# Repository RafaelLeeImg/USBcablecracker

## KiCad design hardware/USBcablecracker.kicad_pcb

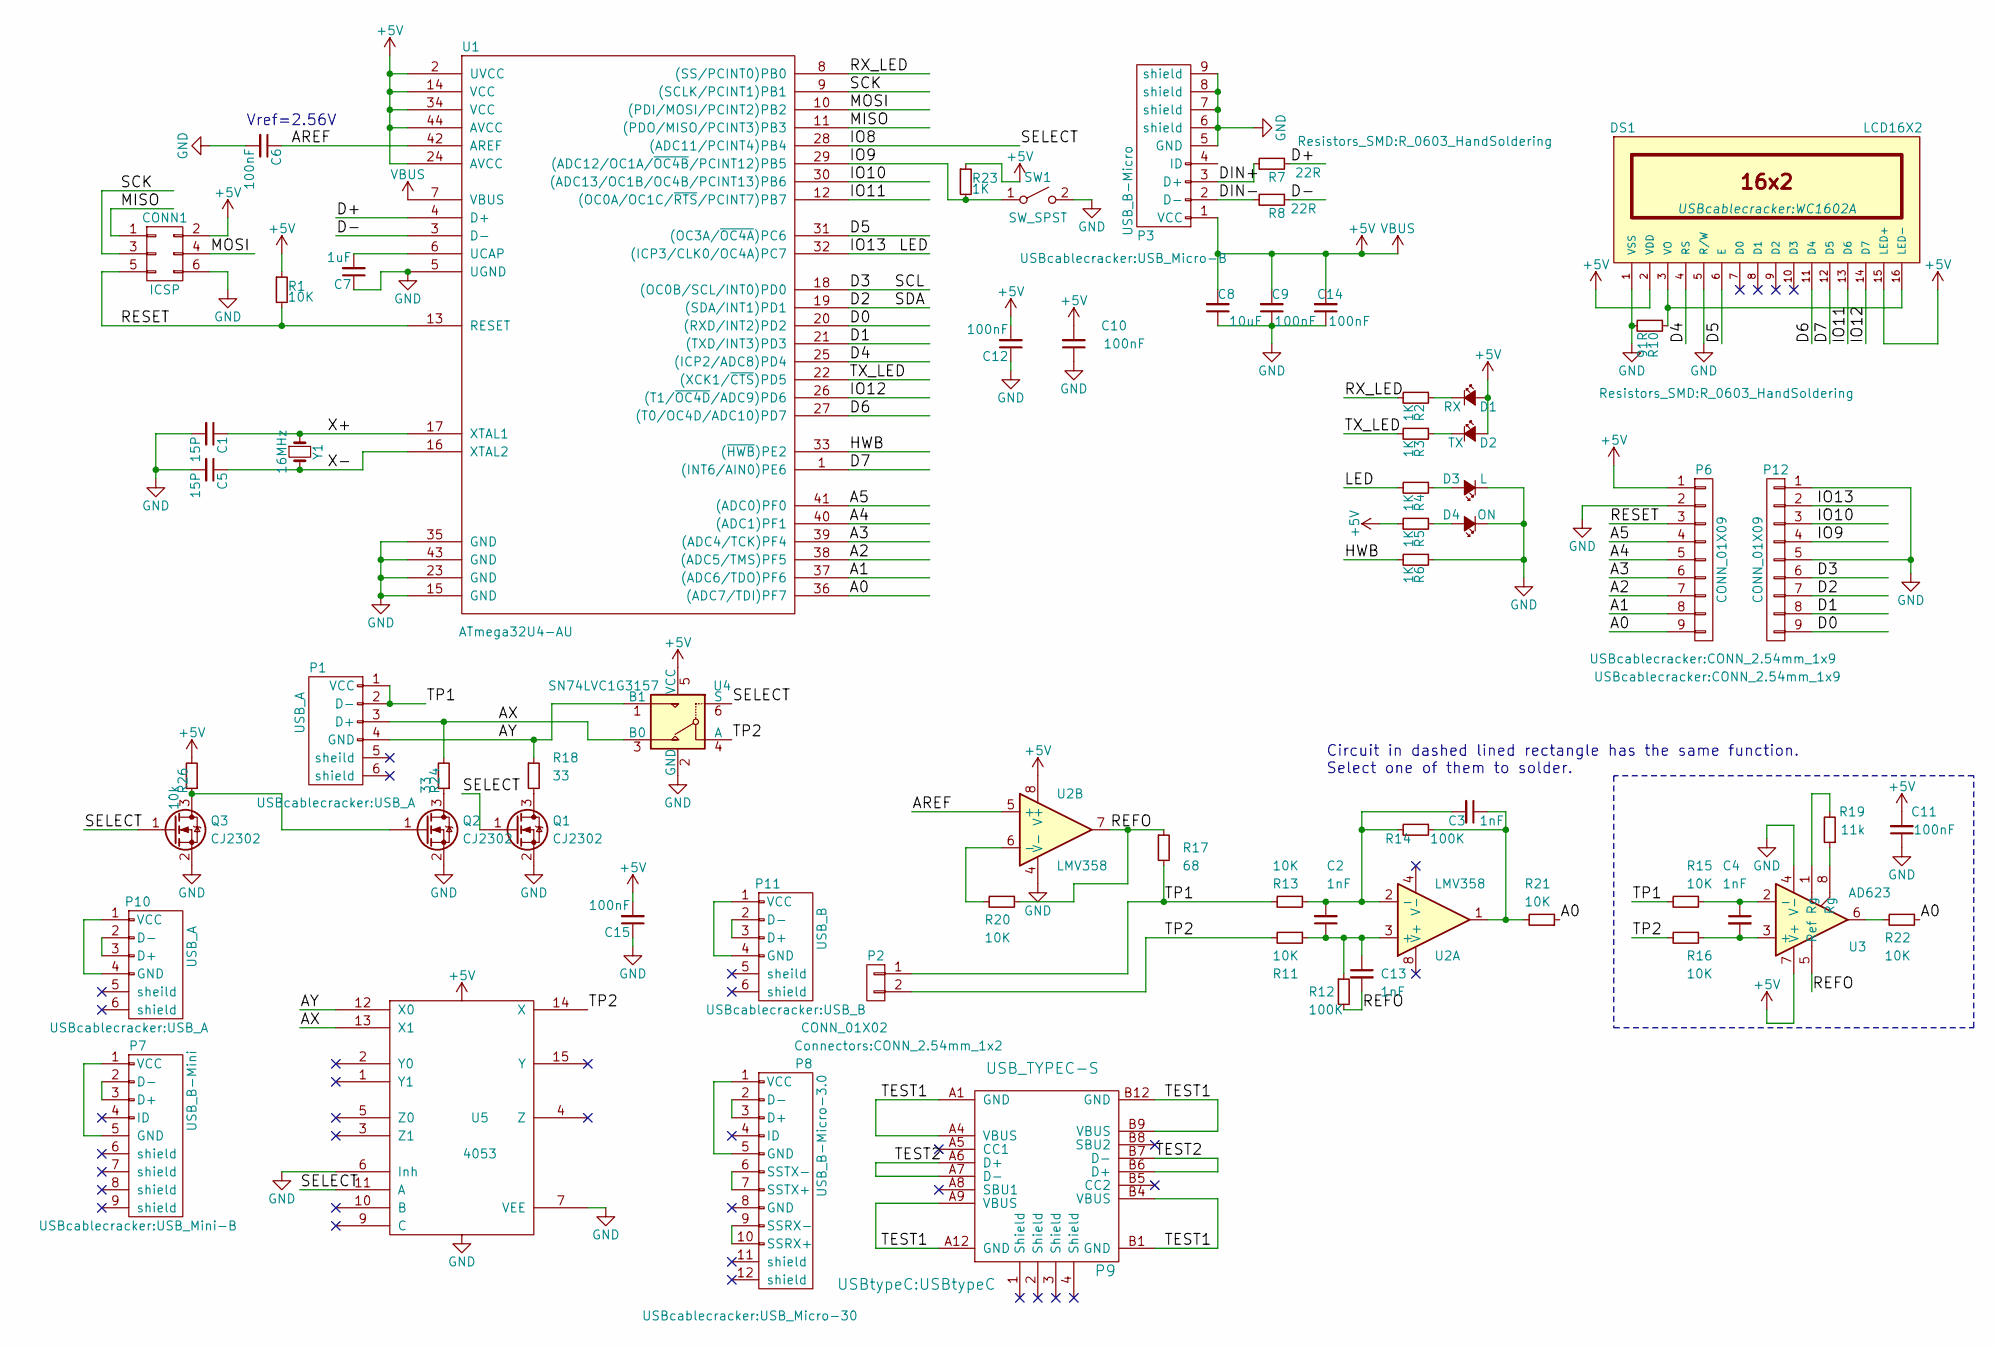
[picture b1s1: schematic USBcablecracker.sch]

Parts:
C1, C5: 15P; C_0603_HandSoldering
C2, C3, C4, C13: 1nF; C_0603_HandSoldering
C6, C9, C10, C11, C12, C14, C15: 100nF; C_0603_HandSoldering
C7: 1uF; C_0603_HandSoldering
C8: 10uF; C_0603_HandSoldering
CONN1: ICSP; CONN_2.54mm_2x3
D1: RX; LED_0603
D2: TX; LED_0603
D3: L; LED_0603
D4: ON; LED_0603
DS1: LCD16X2; WC1602A
P1, P10: USB_A
P2: CONN_01X02; CONN_2.54mm_1x2
P3: USB_B-Micro; USB_Micro-B
P6, P12: CONN_01X09; CONN_2.54mm_1x9
P7: USB_B-Mini; USB_Mini-B
P8: USB_B-Micro-3.0; USB_Micro-30
P9: USB_TYPEC-S; USBtypeC
P11: USB_B
Q1, Q2, Q3: CJ2302; SOT-23_Handsoldering
R1, R11, R13, R15, R16, R20, R21, R22: 10K; R_0603_HandSoldering
R2, R3, R4, R5, R6, R23: 1K; R_0603_HandSoldering
R7, R8: 22R; R_0603_HandSoldering
R10: 91R; R_0603_HandSoldering
R12, R14: 100K; R_0603_HandSoldering
R17: 68; R_0603_HandSoldering
R18, R24: 33; R_0603_HandSoldering
R19: 11k; R_0603_HandSoldering
R26: 10k; R_0603_HandSoldering
SW1: SW_SPST; SW_SPST_EVQP0
U1: ATmega32U4-AU; TQFP-44_10x10mm_Pitch0.8mm
U2: LMV358; SOIC-8_3.9x4.9mm_Pitch1.27mm
U3: AD623; SOIC-8_3.9x4.9mm_Pitch1.27mm
U4: SN74LVC1G3157; SOT-23-6_Handsoldering
U5: 4053; TSSOP-16_4.4x5mm_Pitch0.65mm
Y1: 16MHz; crystal_FA238-TSX3225

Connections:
+5C: C8.2, C9.2, C10.2, C11.2, C12.2, C14.2, C15.2, CONN1.2, D1.2 (A), D2.2 (A), DS1.2 (VDD), DS1.15 (LED+), P3.1 (VCC), P6.1, R1.1, R5.2, R23.1, R26.2, U1.2 (UVCC), U1.7 (VBUS), U1.14 (VCC), U1.24 (AVCC), U1.34 (VCC), U1.44 (AVCC), U2.8 (V+), U3.7 (V+), U4.5 (VCC), U5.16 (VDD)
/A0: P6.9, R21.1, R22.1, U1.36 ((ADC7/TDI)PF7)
/A1: P6.8, U1.37 ((ADC6/TDO)PF6)
/A2: P6.7, U1.38 ((ADC5/TMS)PF5)
/A3: P6.6, U1.39 ((ADC4/TCK)PF4)
/A4: P6.5, U1.40 ((ADC1)PF1)
/A5: P6.4, U1.41 ((ADC0)PF0)
/AREF: C6.1, U1.42 (AREF), U2.5 (+)
/AX: P1.3 (D+), R24.2, U4.3 (B0), U5.13 (X1)
/AY: P1.4 (GND), R18.1, U4.1 (B1), U5.12 (X0)
/D0: P12.9, U1.20 ((RXD/INT2)PD2)
/D1: P12.8, U1.21 ((TXD/INT3)PD3)
/D2: P12.7, U1.19 ((SDA/INT1)PD1)
/D3: P12.6, U1.18 ((OC0B/SCL/INT0)PD0)
/D4: DS1.4 (RS), U1.25 ((ICP2/ADC8)PD4)
/D5: DS1.6 (E), U1.31 ((OC3A/~OC4A~)PC6)
/D6: DS1.11 (D4), U1.27 ((T0/OC4D/ADC10)PD7)
/D7: DS1.12 (D5), U1.1 ((INT6/AIN0)PE6)
/D+: R7.1, U1.4 (D+)
/D-: R8.1, U1.3 (D-)
/DIN+: P3.3 (D+), R7.2
/DIN-: P3.2 (D-), R8.2
/HWB: R6.2, U1.33 ((~HWB~)PE2)
/IO8: Q1.1 (G), Q3.1 (G), U1.28 ((ADC11/PCINT4)PB4), U4.6 (S), U5.11 (A)
/IO9: P12.4, R23.2, SW1.1 (A), U1.29 ((ADC12/OC1A/~OC4B~/PCINT12)PB5)
/IO10: P12.3, U1.30 ((ADC13/OC1B/OC4B/PCINT13)PB6)
/IO11: DS1.13 (D6), U1.12 ((OC0A/OC1C/~RTS~/PCINT7)PB7)
/IO12: DS1.14 (D7), U1.26 ((T1/~OC4D~/ADC9)PD6)
/IO13: P12.2, R4.2, U1.32 ((ICP3/CLK0/OC4A)PC7)
/MISO: CONN1.1, U1.11 ((PDO/MISO/PCINT3)PB3)
/MOSI: CONN1.4, U1.10 ((PDI/MOSI/PCINT2)PB2)
/REFO: C13.2, R12.2, R17.1, R20.1, U2.7, U3.5 (Ref)
/RESET: CONN1.5, P6.3, R1.2, U1.13 (RESET)
/RX_LED: R2.2, U1.8 ((SS/PCINT0)PB0)
/SCK: CONN1.3, U1.9 ((SCLK/PCINT1)PB1)
/TEST1: P9.A1 (GND), P9.A4 (VBUS), P9.A9 (VBUS), P9.A12 (GND), P9.B1 (GND), P9.B4 (VBUS), P9.B9 (VBUS), P9.B12 (GND)
/TEST2: P9.A6 (D+), P9.A7 (D-), P9.B6 (D+), P9.B7 (D-)
/TP1: P1.1 (VCC), P1.2 (D-), P2.1, R13.2, R15.2, R17.2
/TP2: P2.2, R11.2, R16.2, U4.4 (A), U5.14 (X)
/TX_LED: R3.2, U1.22 ((XCK1/~CTS~)PD5)
/X+: C1.1, U1.17 (XTAL1), Y1.1
/X-: C5.1, U1.16 (XTAL2), Y1.2
GND: C1.2, C5.2, C6.2, C7.1, C8.1, C9.1, C10.1, C11.1, C12.1, C14.1, C15.1, CONN1.6, D3.1 (K), D4.1 (K), DS1.1 (VSS), DS1.5 (R/W), P3.5 (GND), P3.6 (shield), P3.7 (shield), P3.8 (shield), P3.9 (shield), P6.2, P12.1, P12.5, Q1.2 (S), Q2.2 (S), Q3.2 (S), R6.1, R10.2, SW1.2 (B), U1.5 (UGND), U1.15 (GND), U1.23 (GND), U1.35 (GND), U1.43 (GND), U2.4 (V-), U3.4 (V-), U4.2 (GND), U5.6 (Inh), U5.7 (VEE), U5.8 (VSS)
unnamed: C2.2, C3.2, R13.1, R14.2, U2.2 (-)
unnamed: C3.1, R14.1, R21.2, U2.1
unnamed: C4.1, R15.1, U3.2 (-)
unnamed: C4.2, R16.1, U3.3 (+)
unnamed: C7.2, U1.6 (UCAP)
unnamed: C2.1, C13.1, R11.1, R12.1, U2.3 (+)
unnamed: D1.1 (K), R2.1
unnamed: D2.1 (K), R3.1
unnamed: D3.2 (A), R4.1
unnamed: D4.2 (A), R5.1
unnamed: DS1.3 (VO), DS1.16 (LED-), R10.1
unnamed: P7.1 (VCC), P7.5 (GND)
unnamed: P7.2 (D-), P7.3 (D+)
unnamed: P8.1 (VCC), P8.5 (GND)
unnamed: P8.2 (D-), P8.3 (D+)
unnamed: P8.6 (SSTX-), P8.7 (SSTX+)
unnamed: P8.9 (SSRX-), P8.10 (SSRX+)
unnamed: P10.1 (VCC), P10.4 (GND)
unnamed: P10.2 (D-), P10.3 (D+)
unnamed: P11.1 (VCC), P11.4 (GND)
unnamed: P11.2 (D-), P11.3 (D+)
unnamed: Q1.3 (D), R18.2
unnamed: Q2.1 (G), Q3.3 (D), R26.1
unnamed: Q2.3 (D), R24.1
unnamed: R19.1, U3.8 (Rg)
unnamed: R19.2, U3.1 (Rg)
unnamed: R20.2, U2.6 (-)
unnamed: R22.2, U3.6

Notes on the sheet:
Circuit in dashed lined rectangle has the same function. Select one of them to solder.
Vref=2.56V

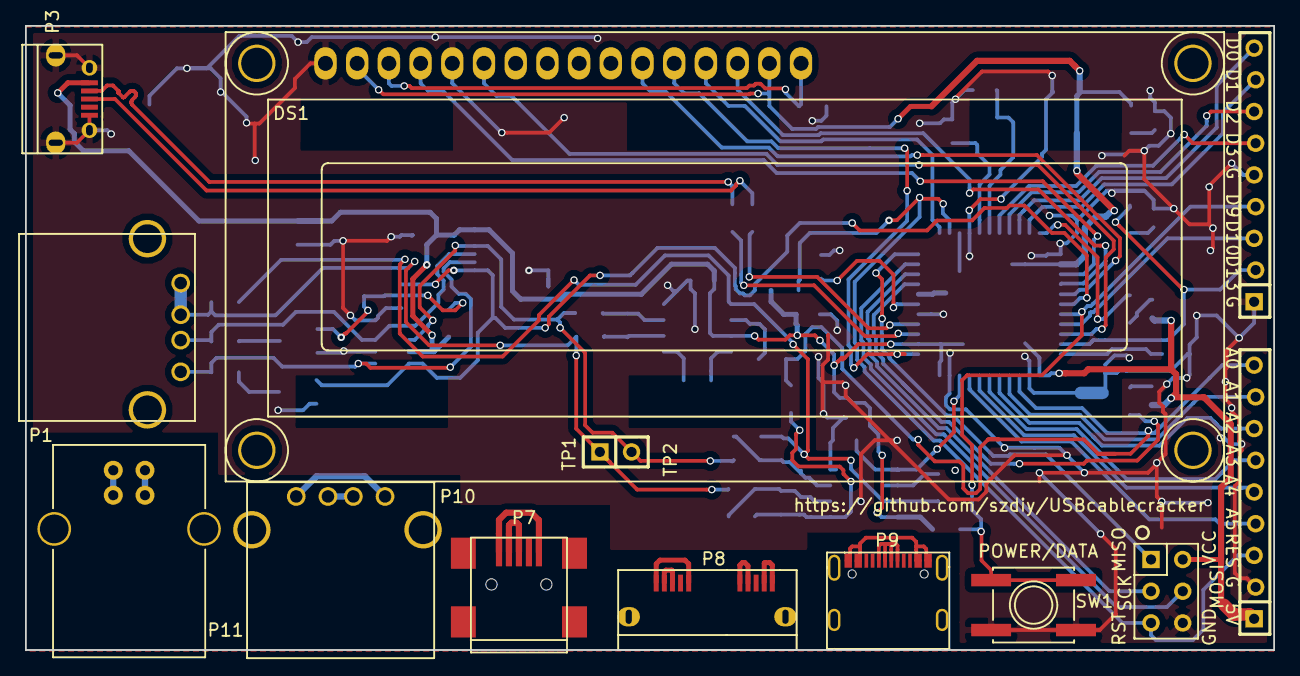
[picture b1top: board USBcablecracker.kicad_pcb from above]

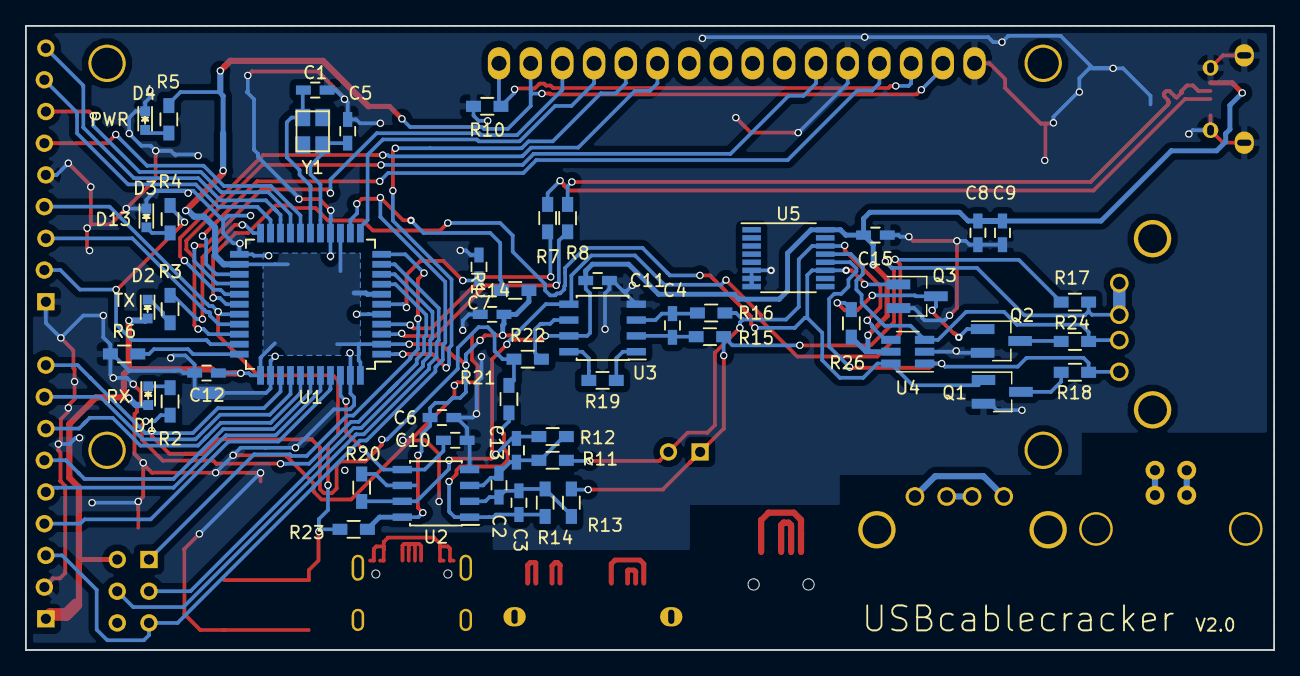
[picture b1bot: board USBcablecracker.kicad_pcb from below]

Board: 2 copper layers, 100.0 x 50.0 mm, 65 parts (52 on the bottom side), 71 nets.

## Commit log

2018-10-05 Modify PCB to v2.0, delete switch, add an analog switch and a button instead.
